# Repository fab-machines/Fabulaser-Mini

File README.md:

<div align="center"><h1 style=align="center">Fabulaser Mini V3</h1></div>
<div align="center"><i>An open source laser cutter within your reach.</i></div>

<br>
<div align="center"></div>

Introduction 
---
Fabulaser Mini is a compact, yet  powerful, open source laser cutter. Developed to fit in Fab Labs and classrooms, Fabulaser Mini aims to lower the boundaries of accessing laser cutting technology, representing an ideal compromise between performance and cost. With an optimized 40W CO2 laser, it is able to cut 8mm acrylic, and with a cutting area of 600x400mm is one the largest of this machine category. The compact machine size of 1161x812x390mm, allows the usage in small rooms with a normal table or a desk.

<div align="center"></div>
<br>

A tool to make, a tool to learn.
--

<div align="center"> </div>

In comparison to commercial laser cutters, Fabulaser Mini adds on top of the laser cutting functionalities a valuable learning experience. Ideally built together with students during a workshop, Fabulaser Mini will give to the user not only the possibility to laser cut, but also to learn how the machine is made, how it works. And other than learning about electronics, mechanics and lasers, the final user will also have a deep knowledge of the machine, so to be able to efficiently execute maintenance, apply improvements and even design his own machine later on!

The Assembly Manual 
--

The Fabulaser Mini assembly manual is an interactive 3D assembly guideline, where the user can learn how to build the laser-cutter, step-by-step. It contains a list of parts, tools, and instruction remarks, following a logic order to provide a smooth assembly experience.

- **[Assembly Manual](https://fab-machines.github.io/Fabulaser-Mini)**

The Kit
--

Fabulaser Mini kit, is the one-stop solution for everything you need to fully use the laser cutting capabilities of Fabulaser Mini. Providing all the required parts and special tools to build the laser cutter, Fabulaser Mini kit also provides all the additional accessories to start laser cutting out of the box. As well as all the required adapters and connections are provided, so that the user only have to concentrate on assembly, without losing time in searching and buying additional parts.

Included in the Fabulaser Kit:

- Fabulaser Mini machine parts
- air assist compressor
- exhaust radial fan
- indoor air filter
- water chiller
- all the required connections/adapters

More info on Fabulaser Mini are available at: [http://fabulaser.net/](http://fabulaser.net/)

Fabulaser Mini V3 specifications
--
<div align="center"></div>
<br>

- laser source: 40W CO2
- cutting area: 600x400mm
- resolution: 0.05mm 
- max. cutting thickness: 
  - 10mm acrylic
  - 6mm MDF
  - 8mm Plywood
- max speed: 1000mm/s
- motion: linear rails and linear shafts
- frame and housing: interlocked aluminum plates
- bed: aluminum lamella
- sensors: inductive probes
- controller: 32bit Teensy 4.1
- firmware: [grbl-hal]([https://github.com/cprezzi/grbl-LPC](https://github.com/grblHAL/iMXRT1062))
- machine dimensions: 1161x812x390mm

Files
--

- **[BOM](Fabulaser_Mini_V3_BOM.pdf)**
- **[Firmware](firmware)**
- **[CAD](cad)**
- **[Settings](settings)**
- **[Workbook](Fabulaser_Mini_V3_Workbook.pdf)**
- **[Wiring Schematic](WiringSchematic_FabulaserMini_V3.pdf)**
- **[Assembly Manual (Fabulaser Mini V2)](Fabulaser_Mini_V2_manual_L2M2.pdf)**

Authors
--

Fabulaser Mini has been designed, developed and manufactured by:<br>

- **Daniele Ingrassia, daniele@inmachines.net**
- **[InMachines Ingrassia GmbH](https://www.inmachines.net/)**<br>

License
--

The Fabulaser Mini hardware design, CAD and PCB files, BOM, settings and relative files are are released under the following open source license:

- CERN Open Hardware Licence Version 2 Weakly Reciprocal - **[CERN-OHL-W](LICENSE_CERN_OHL_W_V2.txt)**

The Fabulaser assembly manual, pictures and presentation text of this repository are released under the following license:

- Creative-Commons-Attribution-ShareAlike 4.0 International - **[CC BY-SA 4.0](LICENSE_CC_BY_SA_4.0.txt)**

Fabulaser Mini uses grbl-LPC [https://github.com/cprezzi/grbl-LPC](https://github.com/cprezzi/grbl-LPC), released under the [GPLv3 license](https://www.gnu.org/licenses/gpl-3.0.en.html).

Previous version
--

Previous versions of Fabulaser Mini will always be available. 

**[Fabulaser Mini V2 Repository](Fabulaser_Mini_V2)** 
<div></div>

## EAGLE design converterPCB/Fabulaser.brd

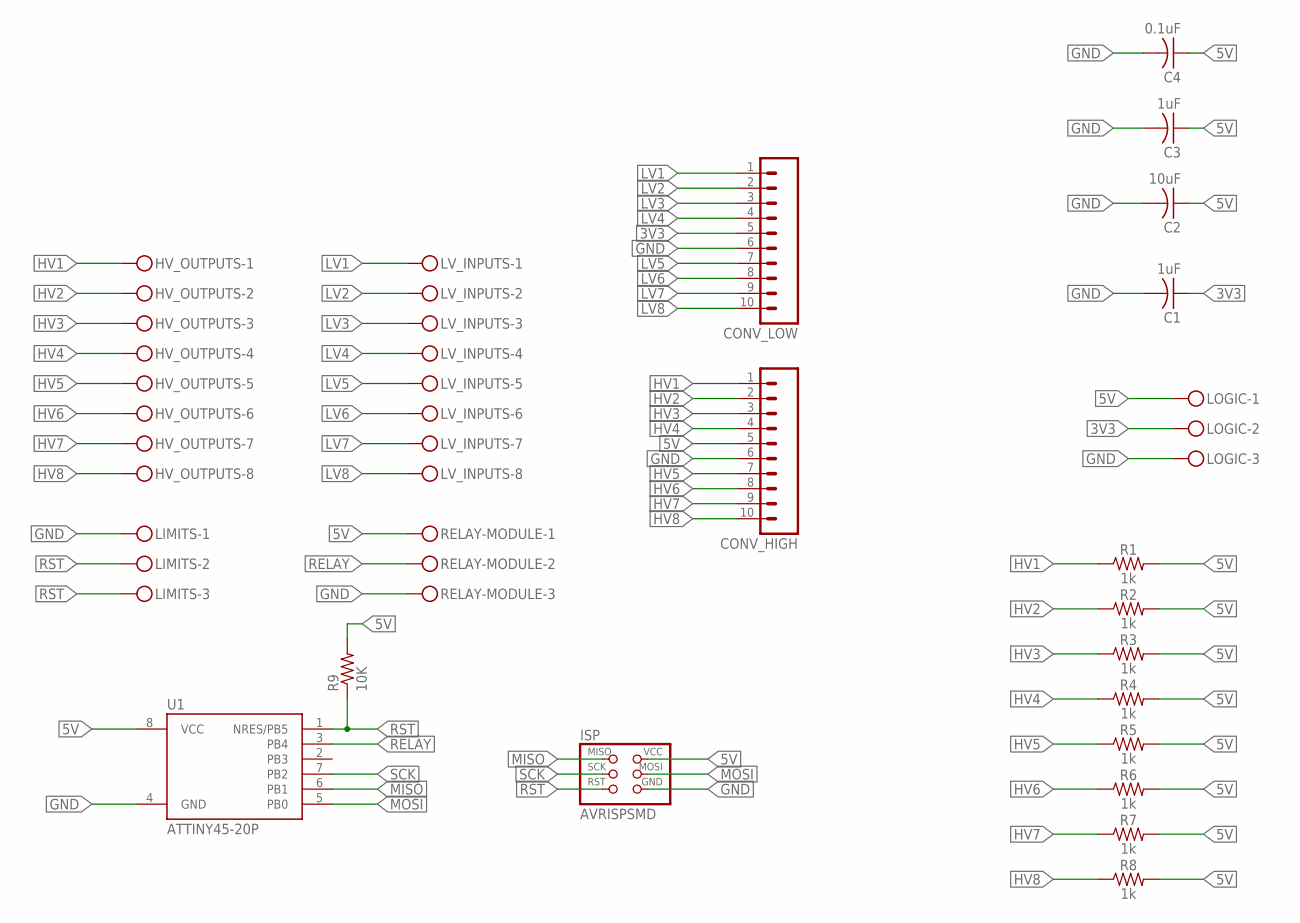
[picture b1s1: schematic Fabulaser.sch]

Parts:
C1, C3: 1uF; C1206FAB
C2: 10uF; C1206FAB
C4: 0.1uF; C1206FAB
CONV_HIGH: M10; 10P
CONV_LOW: M10; 10P
HV_OUTPUTS: MKDSN1,5/8-5,08
ISP: AVRISPSMD; 2X03SMD
LIMITS: MKDSN1,5/3-5,08
LOGIC: MKDSN1,5/3-5,08
LV_INPUTS: MKDSN1,5/8-5,08
R1, R2, R3, R4, R5, R6, R7, R8: 1k; AXIAL-0.3
R9: 10K; R1206FAB
RELAY-MODULE: MKDSN1,5/3-5,08
U1: ATTINY45-20P; PDIP08_300MIL

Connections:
3V3: C1.1, CONV_LOW.5, LOGIC.2
5V: C2.1, C3.1, C4.1, CONV_HIGH.5, ISP.2 (VCC), LOGIC.1, R1.P$2 (2), R2.P$2 (2), R3.P$2 (2), R4.P$2 (2), R5.P$2 (2), R6.P$2 (2), R7.P$2 (2), R8.P$2 (2), R9.2, RELAY-MODULE.1, U1.8 (VCC)
GND: C1.2, C2.2, C3.2, C4.2, CONV_HIGH.6, CONV_LOW.6, ISP.6 (GND), LIMITS.1, LOGIC.3, RELAY-MODULE.3, U1.4 (GND)
HV1: CONV_HIGH.1, HV_OUTPUTS.1, R1.P$1 (1)
HV2: CONV_HIGH.2, HV_OUTPUTS.2, R2.P$1 (1)
HV3: CONV_HIGH.3, HV_OUTPUTS.3, R3.P$1 (1)
HV4: CONV_HIGH.4, HV_OUTPUTS.4, R4.P$1 (1)
HV5: CONV_HIGH.7, HV_OUTPUTS.5, R5.P$1 (1)
HV6: CONV_HIGH.8, HV_OUTPUTS.6, R6.P$1 (1)
HV7: CONV_HIGH.9, HV_OUTPUTS.7, R7.P$1 (1)
HV8: CONV_HIGH.10, HV_OUTPUTS.8, R8.P$1 (1)
LV1: CONV_LOW.1, LV_INPUTS.1
LV2: CONV_LOW.2, LV_INPUTS.2
LV3: CONV_LOW.3, LV_INPUTS.3
LV4: CONV_LOW.4, LV_INPUTS.4
LV5: CONV_LOW.7, LV_INPUTS.5
LV6: CONV_LOW.8, LV_INPUTS.6
LV7: CONV_LOW.9, LV_INPUTS.7
LV8: CONV_LOW.10, LV_INPUTS.8
MISO: ISP.1 (MISO), U1.6 (PB1)
MOSI: ISP.4 (MOSI), U1.5 (PB0)
RELAY: RELAY-MODULE.2, U1.3 (PB4)
RST: ISP.5 (RST), LIMITS.2, LIMITS.3, R9.1, U1.1 (NRES/PB5)
SCK: ISP.3 (SCK), U1.7 (PB2)

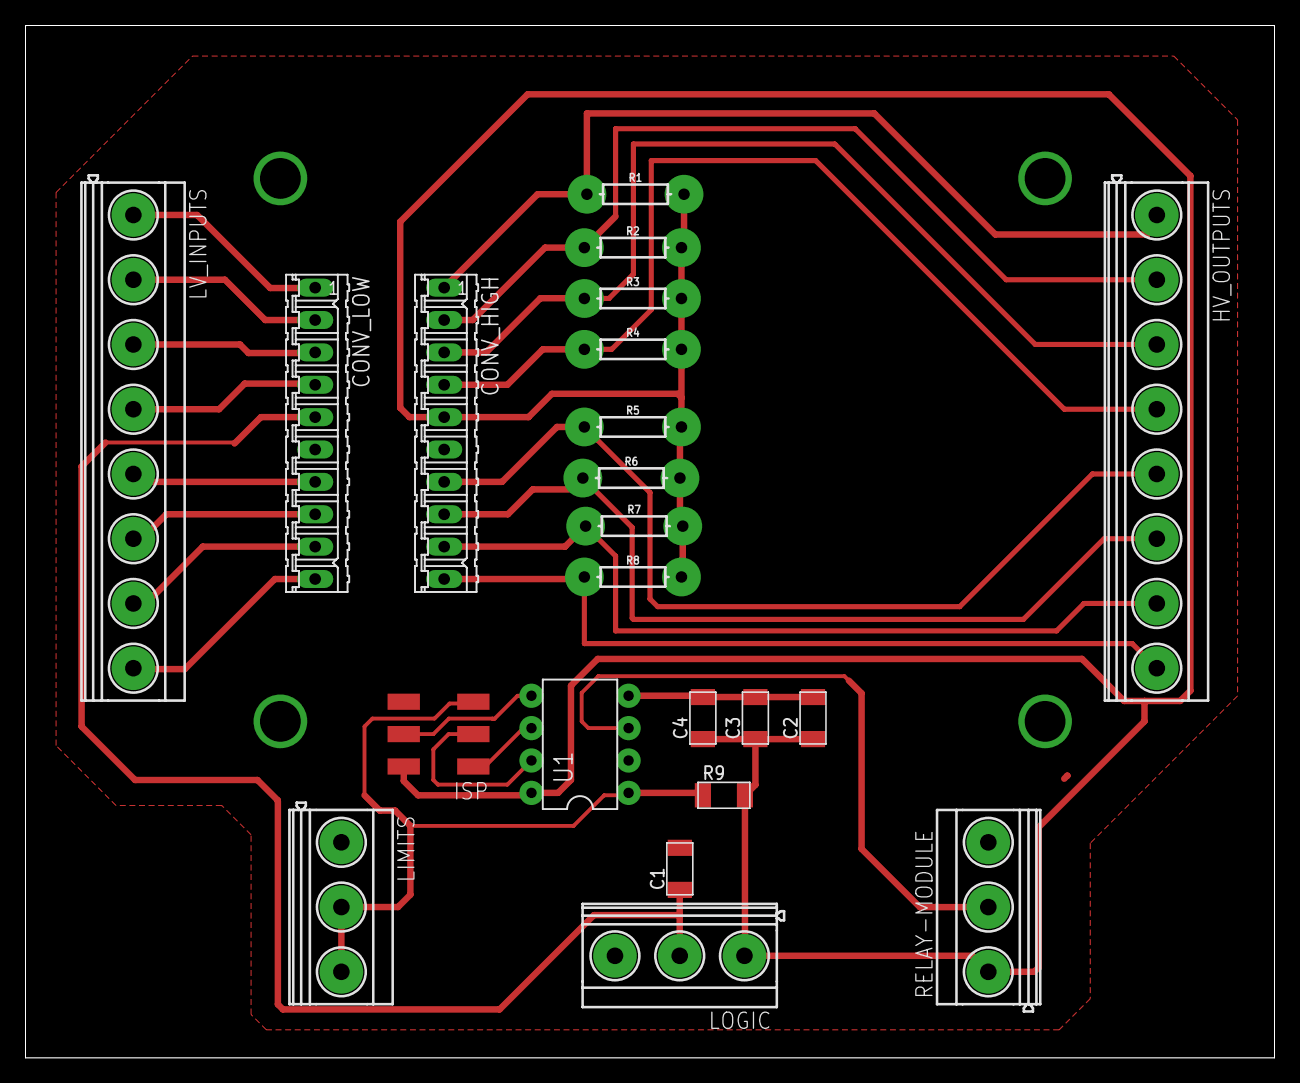
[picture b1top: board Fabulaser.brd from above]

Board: 2 copper layers, 98.0 x 81.0 mm, 22 parts (0 on the bottom side), 24 nets.

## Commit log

2021-11-03 added initial description, license, authors and pictures
2021-11-03 added licenses
2021-11-03 linked images
2021-11-03 added BOM, firmware and updated readme
2021-11-03 zipped firmware
2021-11-03 added CAD files, converter PCB
2021-11-03 updated grbl defaults
2021-11-03 added manual
2021-11-04 adding French readme init
2021-11-04 French RM update
2021-11-04 French RM corrections
2022-05-24 Added template DXF files
2023-01-10 upload user manual
2023-01-10 added user manual
2023-06-15 Update README.md
    added version into repository name
2023-06-15 Fabulaser Mini v2 folder
2023-06-15 Fabulaser Mini V2 Page
2023-06-15 change name
2023-06-15 Update Intro
2023-06-15 add img
2023-06-15 changed image
2023-06-15 upload files
2023-06-16 add manual
2023-11-27 update user manual
2025-08-13 add assembly manual
2025-08-13 update assembly manual
2025-08-27 Assembly Manual json update
2025-08-27 Assembly Manual update package
2025-08-27 Assembly Manual package update
2025-08-27 Assembly Manual update
2026-01-30 added relay code

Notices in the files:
parts and their libraries:
SparkFun-Resistors: Licensing: Creative Commons ShareAlike 4.0 International - https://creativecommons.org/licenses/by-sa/4.0
